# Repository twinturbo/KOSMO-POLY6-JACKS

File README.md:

# KOSMO-POLY6-JACKS

This repository contains KICAD Schematics, PCB and front panel to build a 6 voice jack board for the "Polykit" Inspired 6 Channel Synth in Kosmo Format [Look Mum No Computer LMNK] . The Jack board is intended as an output stage for the main DCO found here https://github.com/twinturbo/KOSMO-POLY6-PICO-DCO

## About KOSMO-POLY6
The [POLY6](https://github.com/twinturbo/KOSMO-POLY6) GIT contains the details of the porject as a whole, this is one module.

Other modules in the line up are

- KOSMO-POLY6-PICO-DCO - Complete [ DCO ](https://github.com/twinturbo/KOSMO-POLY6-PICO-DCO)
- KOSMO-POLY6-DRUID-DCO -(TBD).
- KOSMO-POLY6-JACKS - Complete. [ JACKS ](https://github.com/twinturbo/KOSMO-POLY6-JACKS)
- KOSMO-POLY6-MIX - In design.
- KOSMO-POLY6-ADSR - In Production with JLCPCB.
- KOSMO-POLY6-VCA - In design.
- KOSMO-POLY6-CONTROLS - (TBD).
- KOSMO-POLY6 Filter - (TBD).
- KOSMO-POLY6-PG Programmer - (TBD)
- KOSMO-POLY6-MetricST-Front-Panel - (TBD)

# KOSMO-POLY6-JACKS Details

The JACKS module has no real use in the finished POLY6 design and can be left out, however it can be useful in testing. It could be employed where you need to jump from one case or shelf to another, where having two of these cross patched with standdard 1/4 Leads could be of use ( although power would still need fed to the rest of the modules. 

## Key features

- 6 Jacks for Pulse Out ( normaled to the output header when not jacked )
- 6 Jacks for Ramp Out ( normaled to the output header when not jacked )
- 6 Jacks for Gate ( normaled to the output header when not jacked )
- +5v, +3.3v , +12V , -12V power pass through ( board itself is passive )

## Schematics and PCB
Schematics and PCB and front panle are in KICAD format.

- Front Panel PCB [Front](https://github.com/twinturbo/KOSMO-POLY6-JACKS/tree/master/HARDWARE/FRONT-PANEL)
- Jack PCB [Jack](https://github.com/twinturbo/KOSMO-POLY6-JACKS/tree/master/HARDWARE/JACK-BOARD)

Gerber files for the PCB and Front Panel can be found here [PLOT](https://github.com/twinturbo/KOSMO-POLY6-JACKS/tree/master/HARDWARE/PCB-PRINTS).

## Pictures

# References
- The Original DCO Project [ Original ](https://github.com/polykit/pico-dco)
- The LMNC project thread [ Thread ](https://lookmumnocomputer.discourse.group/t/kosmoing-the-polykit-dco/5878)
- The Publishing Thread of my POLY6 Modules [ Publish thread ](https://lookmumnocomputer.discourse.group/t/kosmo-poly6-releases/5962)
- Kosmo/LMNC forum [ Frorum Home ](https://lookmumnocomputer.discourse.group/)
- LMNC Webpage [ LMNC website](https://www.lookmumnocomputer.com/)
- LMNC Youtube [ LMNC Youetube](https://www.youtube.com/c/LOOKMUMNOCOMPUTER/videos)

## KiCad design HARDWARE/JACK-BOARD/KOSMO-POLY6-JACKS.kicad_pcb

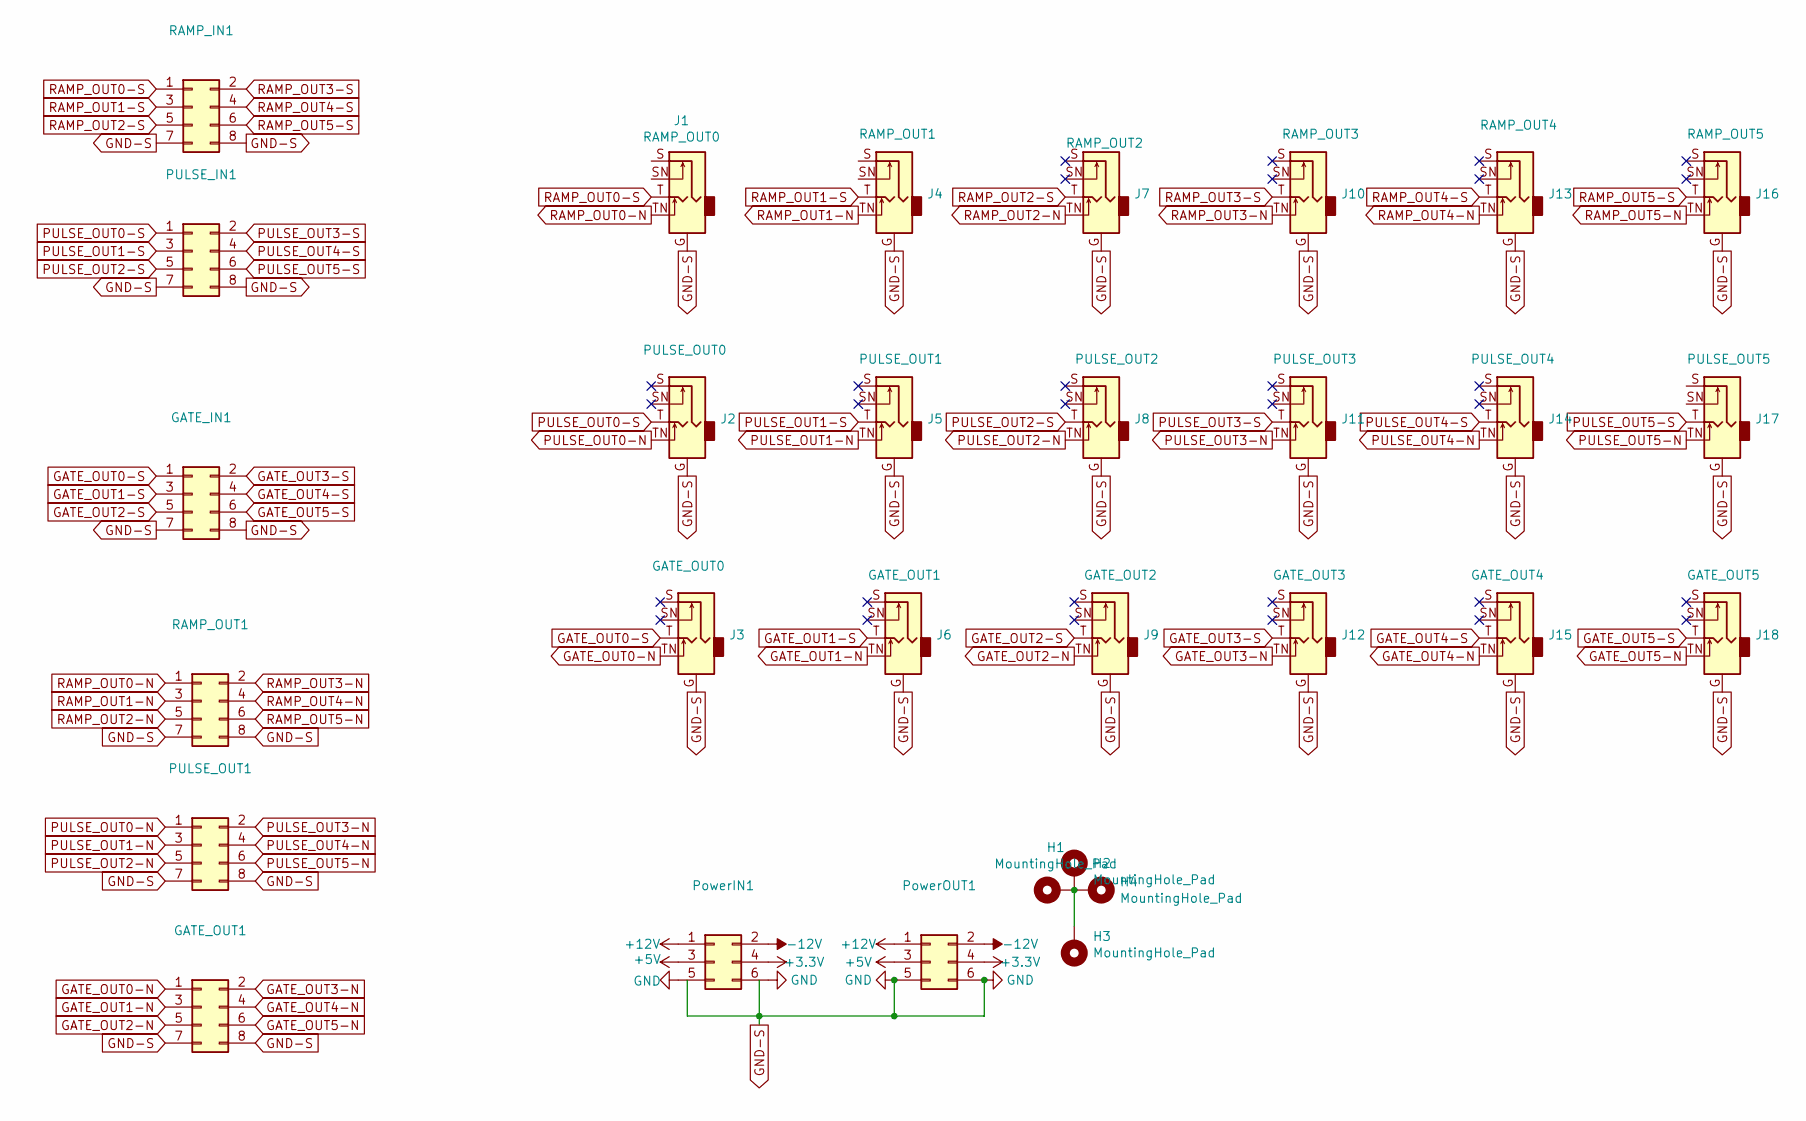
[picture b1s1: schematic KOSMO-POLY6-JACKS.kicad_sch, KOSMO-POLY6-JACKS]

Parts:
GATE_IN1: Conn_02x04_Odd_Even; IDC-Header_2x04_P2.54mm_Vertical
GATE_OUT1: Conn_02x04_Odd_Even; IDC-Header_2x04_P2.54mm_Vertical
H1, H2, H3, H4: MountingHole_Pad; MountingHole_3.2mm_M3_DIN965_Pad
J1: RAMP_OUT0; Jack_6.5mmLMNC
J2: PULSE_OUT0; Jack_6.5mmLMNC
J3: GATE_OUT0; Jack_6.5mmLMNC
J4: RAMP_OUT1; Jack_6.5mmLMNC
J5: PULSE_OUT1; Jack_6.5mmLMNC
J6: GATE_OUT1; Jack_6.5mmLMNC
J7: RAMP_OUT2; Jack_6.5mmLMNC
J8: PULSE_OUT2; Jack_6.5mmLMNC
J9: GATE_OUT2; Jack_6.5mmLMNC
J10: RAMP_OUT3; Jack_6.5mmLMNC
J11: PULSE_OUT3; Jack_6.5mmLMNC
J12: GATE_OUT3; Jack_6.5mmLMNC
J13: RAMP_OUT4; Jack_6.5mmLMNC
J14: PULSE_OUT4; Jack_6.5mmLMNC
J15: GATE_OUT4; Jack_6.5mmLMNC
J16: RAMP_OUT5; Jack_6.5mmLMNC
J17: PULSE_OUT5; Jack_6.5mmLMNC
J18: GATE_OUT5; Jack_6.5mmLMNC
PULSE_IN1: Conn_02x04_Odd_Even; IDC-Header_2x04_P2.54mm_Vertical
PULSE_OUT1: Conn_02x04_Odd_Even; IDC-Header_2x04_P2.54mm_Vertical
PowerIN1: Conn_02x03_Odd_Even; IDC-Header_2x03_P2.54mm_Vertical
PowerOUT1: Conn_02x03_Odd_Even; IDC-Header_2x03_P2.54mm_Vertical
RAMP_IN1: Conn_02x04_Odd_Even; IDC-Header_2x04_P2.54mm_Vertical
RAMP_OUT1: Conn_02x04_Odd_Even; IDC-Header_2x04_P2.54mm_Vertical

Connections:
+3V3: PowerIN1.4, PowerOUT1.4
+5V: PowerIN1.3, PowerOUT1.3
+12V: PowerIN1.1, PowerOUT1.1
-12V: PowerIN1.2, PowerOUT1.2
GATE_OUT0-N: GATE_OUT1.1, J3.TN
GATE_OUT0-S: GATE_IN1.1, J3.T
GATE_OUT1-N: GATE_OUT1.3, J6.TN
GATE_OUT1-S: GATE_IN1.3, J6.T
GATE_OUT2-N: GATE_OUT1.5, J9.TN
GATE_OUT2-S: GATE_IN1.5, J9.T
GATE_OUT3-N: GATE_OUT1.2, J12.TN
GATE_OUT3-S: GATE_IN1.2, J12.T
GATE_OUT4-N: GATE_OUT1.4, J15.TN
GATE_OUT4-S: GATE_IN1.4, J15.T
GATE_OUT5-N: GATE_OUT1.6, J18.TN
GATE_OUT5-S: GATE_IN1.6, J18.T
GND-S: GATE_IN1.7, GATE_IN1.8, GATE_OUT1.7, GATE_OUT1.8, J1.G, J2.G, J3.G, J4.G, J5.G, J6.G, J7.G, J8.G, J9.G, J10.G, J11.G, J12.G, J13.G, J14.G, J15.G, J16.G, J17.G, J18.G, PULSE_IN1.7, PULSE_IN1.8, PULSE_OUT1.7, PULSE_OUT1.8, PowerIN1.5, PowerIN1.6, PowerOUT1.5, PowerOUT1.6, RAMP_IN1.7, RAMP_IN1.8, RAMP_OUT1.7, RAMP_OUT1.8
unnamed: H1.1, H2.1, H3.1, H4.1
PULSE_OUT0-N: J2.TN, PULSE_OUT1.1
PULSE_OUT0-S: J2.T, PULSE_IN1.1
PULSE_OUT1-N: J5.TN, PULSE_OUT1.3
PULSE_OUT1-S: J5.T, PULSE_IN1.3
PULSE_OUT2-N: J8.TN, PULSE_OUT1.5
PULSE_OUT2-S: J8.T, PULSE_IN1.5
PULSE_OUT3-N: J11.TN, PULSE_OUT1.2
PULSE_OUT3-S: J11.T, PULSE_IN1.2
PULSE_OUT4-N: J14.TN, PULSE_OUT1.4
PULSE_OUT4-S: J14.T, PULSE_IN1.4
PULSE_OUT5-N: J17.TN, PULSE_OUT1.6
PULSE_OUT5-S: J17.T, PULSE_IN1.6
RAMP_OUT0-N: J1.TN, RAMP_OUT1.1
RAMP_OUT0-S: J1.T, RAMP_IN1.1
RAMP_OUT1-N: J4.TN, RAMP_OUT1.3
RAMP_OUT1-S: J4.T, RAMP_IN1.3
RAMP_OUT2-N: J7.TN, RAMP_OUT1.5
RAMP_OUT2-S: J7.T, RAMP_IN1.5
RAMP_OUT3-N: J10.TN, RAMP_OUT1.2
RAMP_OUT3-S: J10.T, RAMP_IN1.2
RAMP_OUT4-N: J13.TN, RAMP_OUT1.4
RAMP_OUT4-S: J13.T, RAMP_IN1.4
RAMP_OUT5-N: J16.TN, RAMP_OUT1.6
RAMP_OUT5-S: J16.T, RAMP_IN1.6

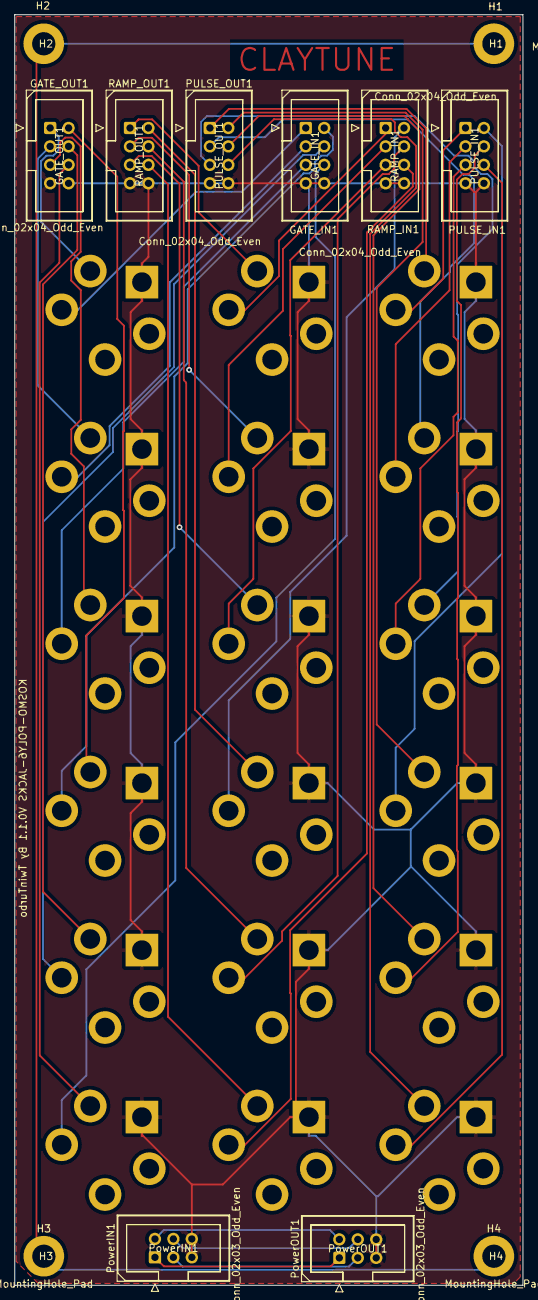
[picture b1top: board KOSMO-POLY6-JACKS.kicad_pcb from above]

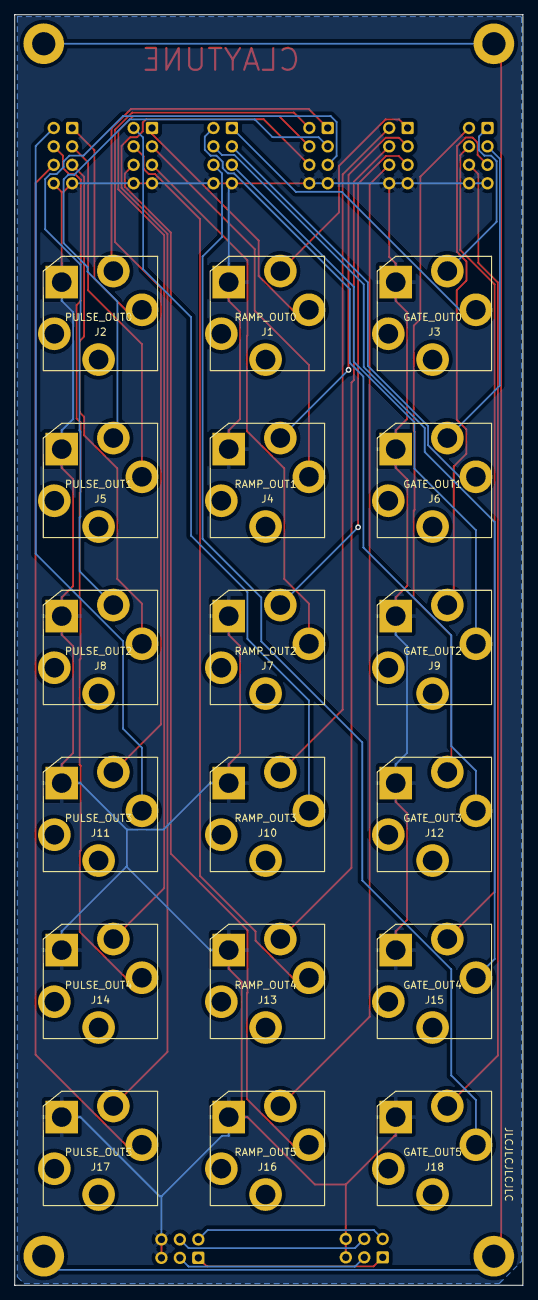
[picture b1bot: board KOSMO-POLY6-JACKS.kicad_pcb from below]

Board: 2 copper layers, 70.0 x 175.0 mm, 30 parts (18 on the bottom side), 42 nets.

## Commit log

2023-03-06 Initialised
2023-03-06 JACKS
2023-03-06 JACKS Seperated
2023-03-07 sync
2023-03-07 Update the readme docs.
2023-03-13 Kicad7 and Fixlayered
2023-05-25 holidaysync
